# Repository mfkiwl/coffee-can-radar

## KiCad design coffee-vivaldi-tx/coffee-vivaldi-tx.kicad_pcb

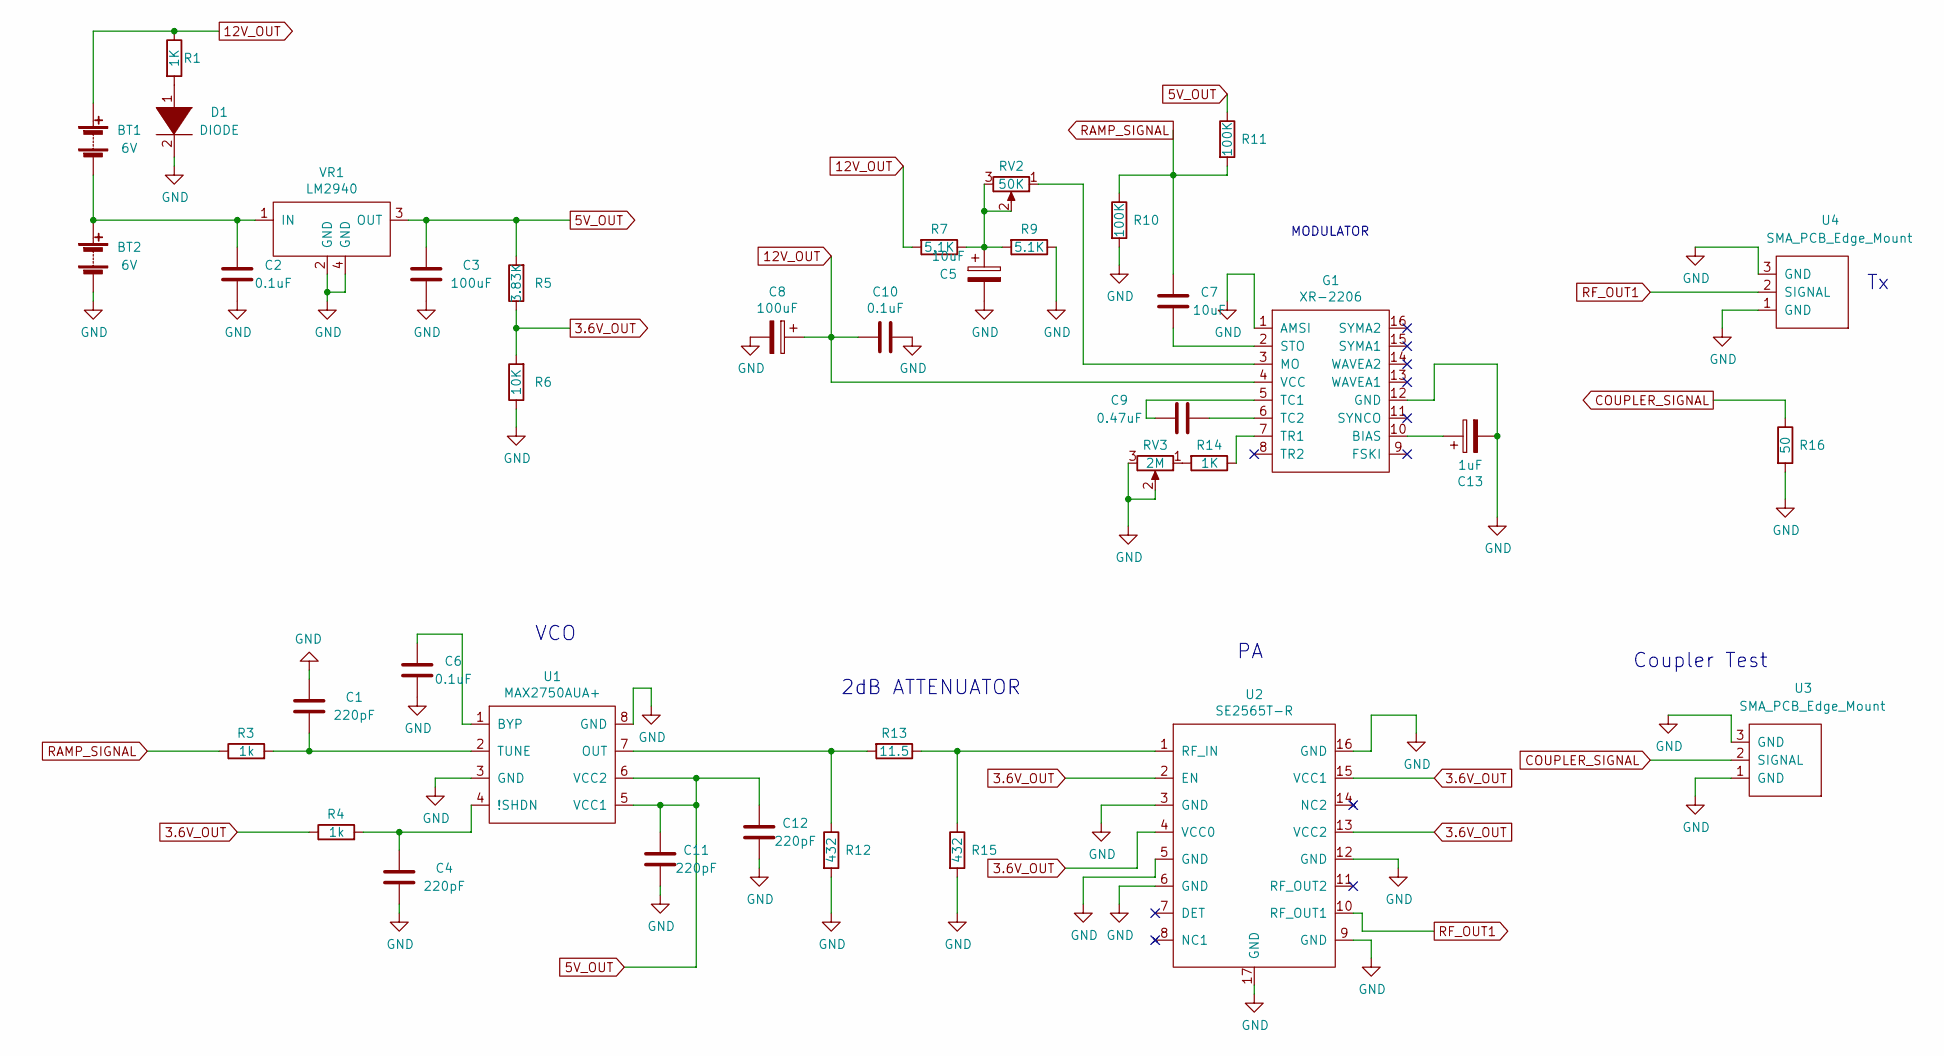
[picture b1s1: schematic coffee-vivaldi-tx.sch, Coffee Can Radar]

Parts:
BT1, BT2: 6V; PinSocket_1x02_P2.54mm_Vertical
C1, C4, C11, C12: 220pF; C_0805_2012Metric
C2, C6, C10: 0.1uF; C_0805_2012Metric
C3: 100uF; C_0805_2012Metric
C5, C7: 10uF; CP_Radial_D5.0mm_P2.50mm
C8: 100uF; CP_Radial_D6.3mm_P2.50mm
C9: 0.47uF; C_0805_2012Metric
C13: 1uF; CP_Radial_D4.0mm_P2.00mm
D1: DIODE; LED_D5.0mm
G1: XR-2206
R1, R14: 1K; R_0805_2012Metric
R3, R4: 1k; R_0805_2012Metric
R5: 3.83K; R_0805_2012Metric
R6: 10K; R_0805_2012Metric
R7, R9: 5.1K; R_0805_2012Metric
R10, R11: 100K; R_0805_2012Metric
R12, R15: 432; R_0805_2012Metric
R13: 11.5; R_0805_2012Metric
R16: 50; R_0805_2012Metric
RV2: 50K; PV36W
RV3: 2M; PV36W
U1: MAX2750AUA+
U2: SE2565T-R
U3, U4: SMA_PCB_Edge_Mount; SMA_EDGE_MOUNT_132255
VR1: LM2940

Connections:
3.6V_OUT: R4.1, R5.1, R6.2, U2.2 (EN), U2.4 (VCC0), U2.13 (VCC2), U2.15 (VCC1)
5V_OUT: C3.1, C11.2, C12.2, R5.2, R11.1, U1.5 (VCC1), U1.6 (VCC2), VR1.3 (OUT)
12V_OUT: BT1.1 (+), C8.1, C10.2, G1.4 (VCC), R1.1, R7.2
COUPLER_SIGNAL: R16.1, U3.2 (SIGNAL)
GND: BT2.2 (-), C1.1, C2.2, C3.2, C4.1, C5.2, C6.2, C8.2, C10.1, C11.1, C12.1, C13.2, D1.2 (A), G1.1 (AMSI), G1.12 (GND), R6.1, R9.1, R10.2, R12.2, R15.2, R16.2, RV3.2, RV3.3, U1.3 (GND), U1.8 (GND), U2.3 (GND), U2.5 (GND), U2.6 (GND), U2.9 (GND), U2.12 (GND), U2.16 (GND), U2.17 (GND), U3.1 (GND), U3.3 (GND), U4.1 (GND), U4.3 (GND), VR1.2 (GND), VR1.4 (GND)
unnamed: BT1.2 (-), BT2.1 (+), C2.1, VR1.1 (IN)
unnamed: C1.2, R3.2, U1.2 (TUNE)
unnamed: C4.2, R4.2, U1.4 (!SHDN)
unnamed: C5.1, R7.1, R9.2, RV2.2, RV2.3
unnamed: C6.1, U1.1 (BYP)
unnamed: C7.2, G1.2 (STO)
unnamed: C9.1, G1.6 (TC2)
unnamed: C9.2, G1.5 (TC1)
unnamed: C13.1, G1.10 (BIAS)
unnamed: D1.1 (K), R1.2
unnamed: G1.3 (MO), RV2.1
unnamed: G1.7 (TR1), R14.1
unnamed: R12.1, R13.2, U1.7 (OUT)
unnamed: R13.1, R15.1, U2.1 (RF_IN)
unnamed: R14.2, RV3.1
RAMP_SIGNAL: C7.1, R3.1, R10.1, R11.2
RF_OUT1: U2.10 (RF_OUT1), U4.2 (SIGNAL)

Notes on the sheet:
2dB ATTENUATOR
VCO
MODULATOR
Coupler Test

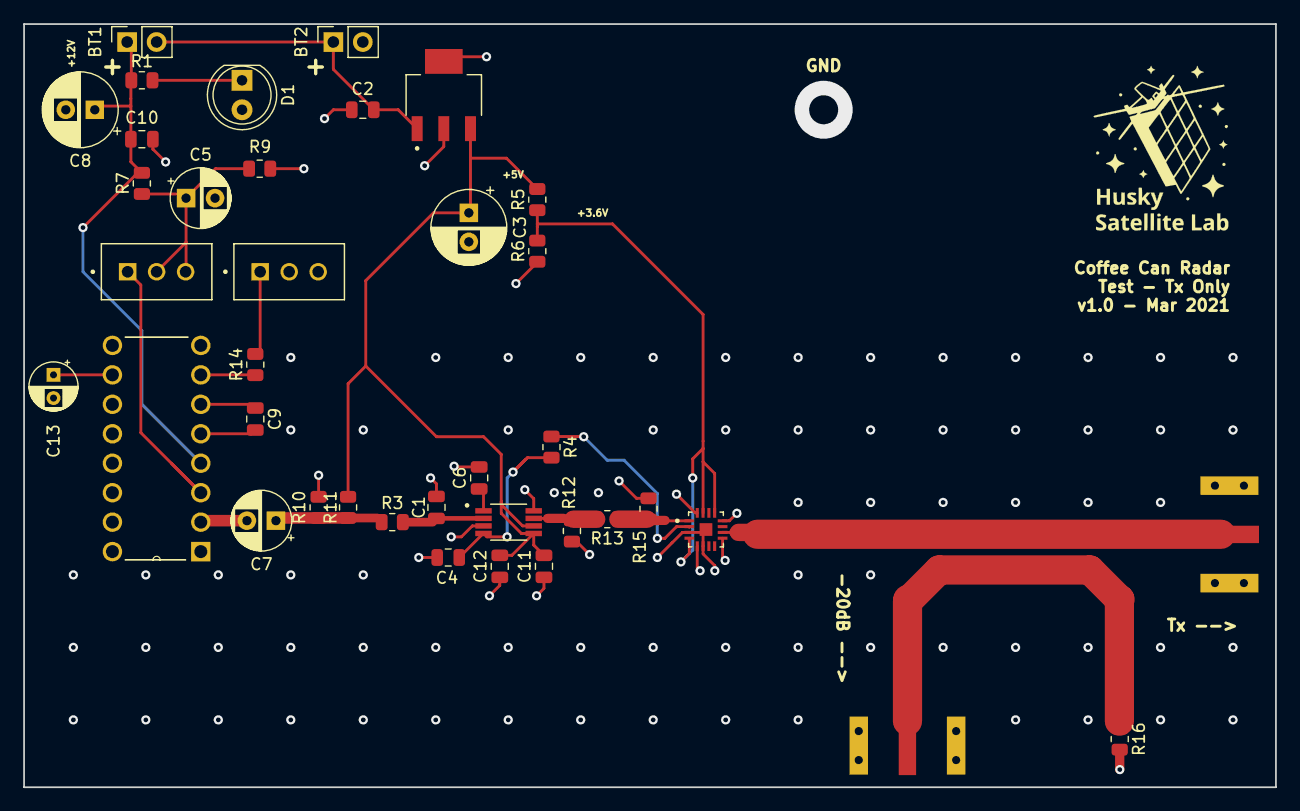
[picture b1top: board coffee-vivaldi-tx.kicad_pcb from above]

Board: 2 copper layers, 108.0 x 65.8 mm, 38 parts (0 on the bottom side), 22 nets.

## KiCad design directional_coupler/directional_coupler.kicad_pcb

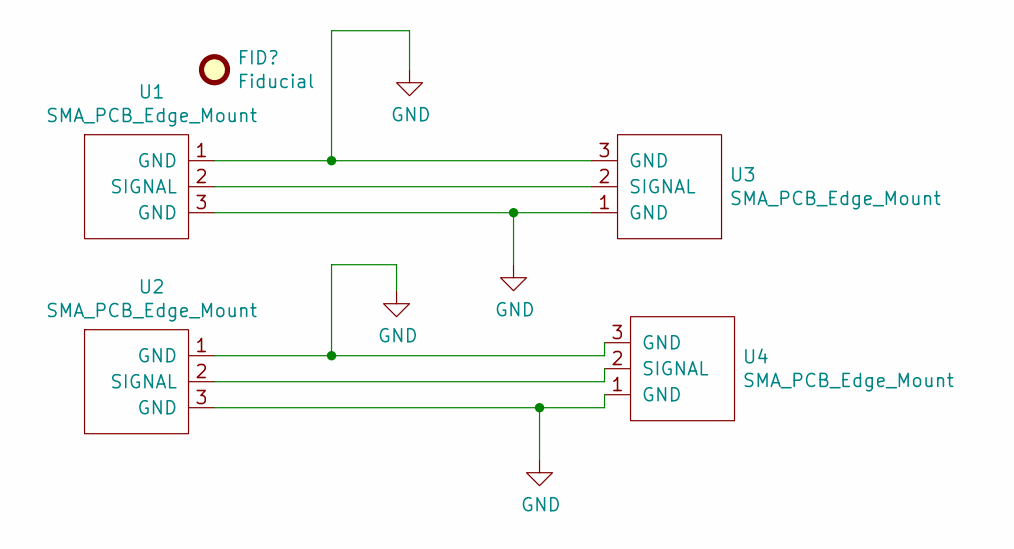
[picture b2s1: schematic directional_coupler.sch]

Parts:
U1, U2, U3, U4: SMA_PCB_Edge_Mount; SMA_EDGE_MOUNT_132255

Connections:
GND: U1.1 (GND), U1.3 (GND), U2.1 (GND), U2.3 (GND), U3.1 (GND), U3.3 (GND), U4.1 (GND), U4.3 (GND)
unnamed: U1.2 (SIGNAL), U3.2 (SIGNAL)
unnamed: U2.2 (SIGNAL), U4.2 (SIGNAL)

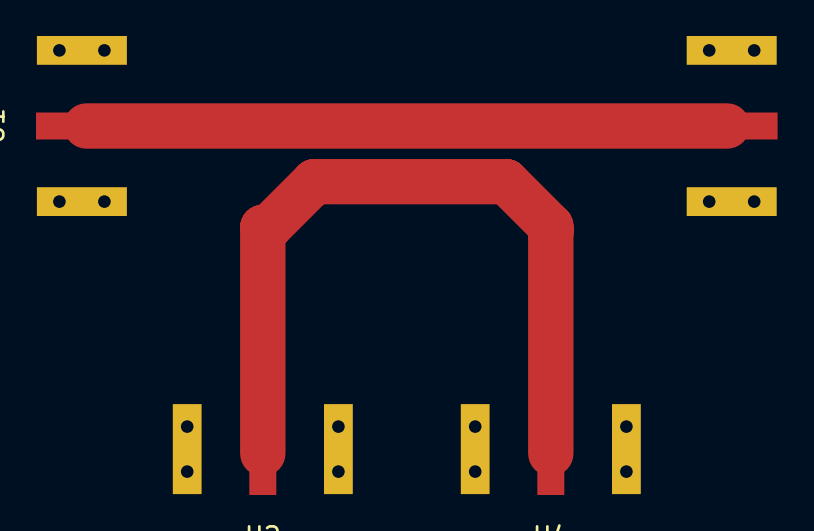
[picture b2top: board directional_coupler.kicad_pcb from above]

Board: 2 copper layers, 4 parts (0 on the bottom side), 3 nets.

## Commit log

2021-01-26 Cleaned up libraries
2021-01-27 Fixed potentiometer symbols, power labels, added Op-Amp OSC1 connected to Ramp_out
2021-02-12 Made symbol for MAAPSS0075 and added vivaldi radar VCO to schematic
2021-02-17 Added chosen RF components to library and schematic
    VCO, PA, and the mixer.
2021-02-23 Adding passive elements with the RF chips
2021-02-25 designed -20dB directional coupler
2021-02-26 Single -20 dB directional coupler
2021-02-26 -20 dB coupler with ground plane
2021-03-01 Added directional coupler for -14, -16, and -18 dB coupled signal gain, added gerber files for manufacturing
2021-03-01 Fixed some silkscreen, put SMA connector pads closer to the edges
2021-03-02 Edited radar schematic
    Still a work in progress.
2021-03-04 Added directional coupler, added impedence control
2021-03-04 Deleted two SMA connectors
2021-03-04 Added voltage dividers
    Still need to work on mixer, LPF, and how to interface the audio jack from a pcb.
2021-03-04 Update coffee-vivaldi.sch
    Current mixer RF input frequency is 2450 MHz, IF output frequency 45 MHz. Will need to double-check if this will affect how we process this signal.
2021-03-06 Created Tx modular radar circuit
    Planning to test transmitting end only to identify any design issues asap.
2021-03-09 Coffee can radar tx update
    Finalized schematic and initial PCB design.
2021-03-11 Tx test board version 1
    Components chosen, board ready for review
2021-03-11 Small edit to Tx PCB
    Smaller area to save space and money :)
2021-03-18 Edited PCB dimensions, added gerber files
2021-03-28 Update schematic and PCB layout
    reference for full design
